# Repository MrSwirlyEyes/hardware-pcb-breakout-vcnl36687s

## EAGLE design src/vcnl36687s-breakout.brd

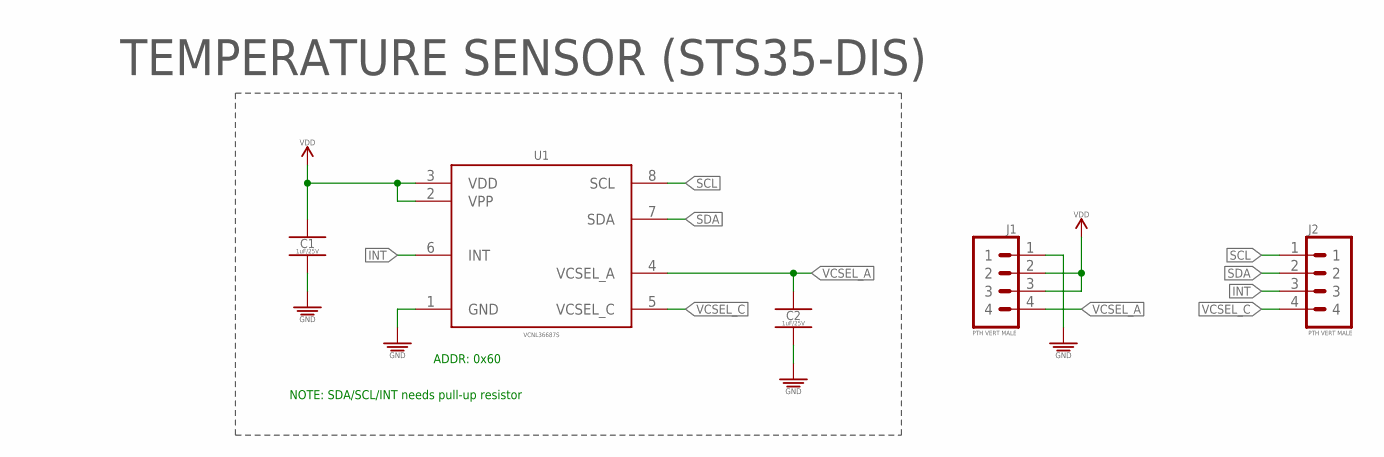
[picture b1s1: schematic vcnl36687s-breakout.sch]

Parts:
C1, C2: 1uF/25V; CAPC1005X55_SMD-0402
J1, J2: PTH VERT MALE; HDRV4W64P254_1X4_1016X254X838B
U1: VCNL36687S; SON77P200X305X100-8N

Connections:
GND: C1.2, C2.2, J1.1, U1.1 (GND)
INT: J2.3, U1.6 (INT)
SCL: J2.1, U1.8 (SCL)
SDA: J2.2, U1.7 (SDA)
VCSEL_A: C2.1, J1.4, U1.4 (VCSEL_A)
VCSEL_C: J2.4, U1.5 (VCSEL_C)
VDD: C1.1, J1.2, J1.3, U1.2 (VPP), U1.3 (VDD)

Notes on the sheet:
TEMPERATURE SENSOR (STS35-DIS)
NOTE: SDA/SCL/INT needs pull-up resistor
ADDR: 0x60

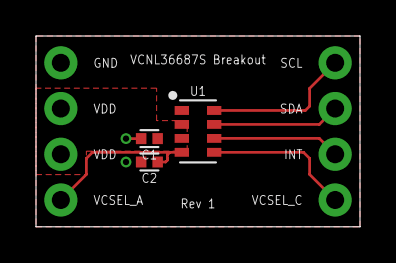
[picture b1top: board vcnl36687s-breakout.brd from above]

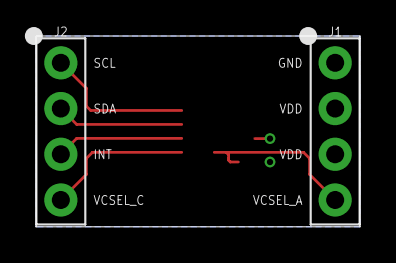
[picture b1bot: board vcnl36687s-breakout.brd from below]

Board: 2 copper layers, 18.0 x 10.6 mm, 5 parts (2 on the bottom side), 7 nets.

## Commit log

2021-08-11 Initialize repo.
